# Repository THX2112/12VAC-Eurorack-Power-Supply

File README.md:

# 12VAC-Eurorack-Power-Supply
A simple +12 -12 power supply for Eurorack using 12VAC adapters

Based on:
http://www.musicfromouterspace.com/analogsynth_new/WALLWARTSUPPLY/WALLWARTSUPPLY.php

http://www.diystompboxes.com/smfforum/index.php?topic=28842.0

http://www.geofex.com/Article_Folders/Power-supplies/powersup.htm

BOM:

6   1n4007     DIODE

1              M05X2SHD        2X5-SHROUDED Header 5x2    

4   1000uF 50V POLARIZED CAPACITOR

2   100uF 35V  POLARIZED CAPACITOR

2   1uF        POLARIZED CAPACITOR

1   2k         RESISTOR

1   7812       TO220       Positive VOLTAGE REGULATOR          

1   7912       TO220       Negative VOLTAGE REGULATOR

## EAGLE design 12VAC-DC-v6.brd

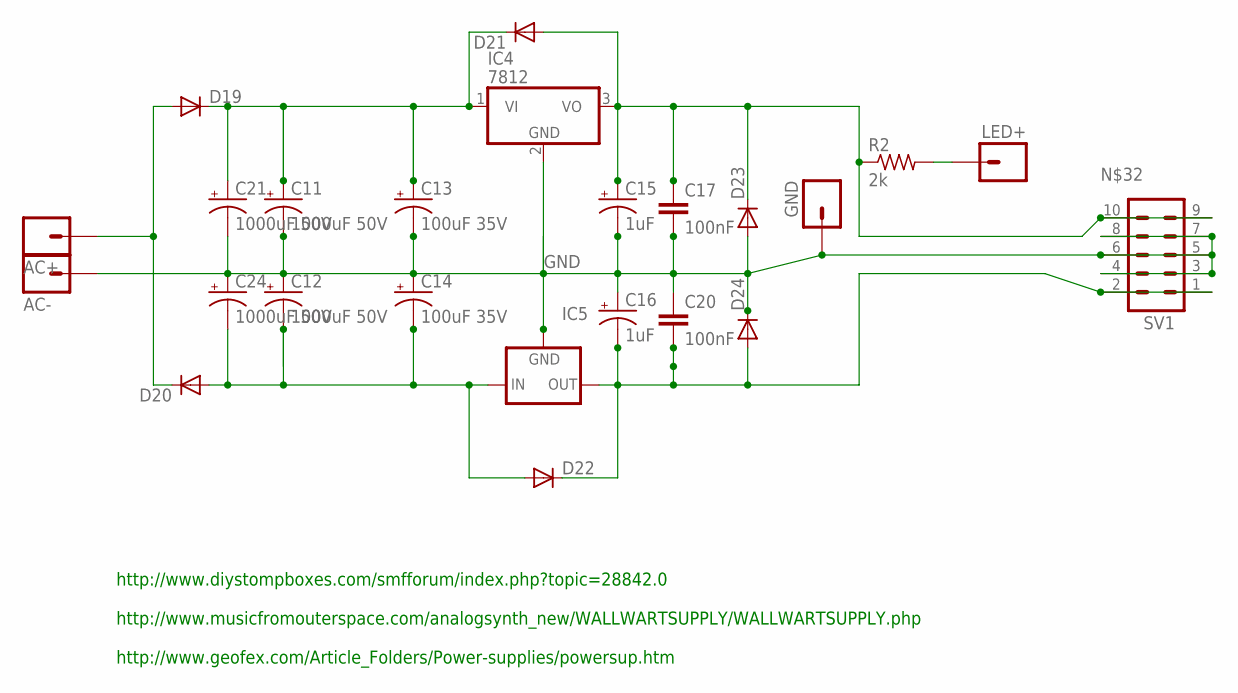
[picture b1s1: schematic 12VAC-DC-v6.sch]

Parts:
C11, C12, C21, C24: 1000uF 50V; E5-13
C13, C14: 100uF 35V; E2,5-6
C15, C16: 1uF; E2,5-5
C17, C20: 100nF; C025-024X044
D19, D20: DIODE-D-7.5; D-7.5
D21, D22, D24: DIODE-D-5; D-5
D23: DIODE-D-2.5; D-2.5
IC4: 7812; TO220V
IC5: 79XXS
JP6: AC+; 1X01_LONGPAD
JP22: AC-; 1X01_LONGPAD
JP25: GND; 1X01_LONGPAD
JP26: LED+; 1X01_LONGPAD
R2: 2k; 0204V
SV1: M05X2SHD; 2X5-SHROUDED

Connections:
GND: C11.-, C12.+, C13.-, C14.+, C15.-, C16.+, C17.2, C20.1, C21.-, C24.+, D23.A, D24.C, IC4.2 (GND), IC5.GND, JP22.1, JP25.1, SV1.3, SV1.4, SV1.5, SV1.6, SV1.7, SV1.8
unnamed: C11.+, C13.+, C21.+, D19.C, D21.C, IC4.1 (VI)
unnamed: C15.+, C17.1, D21.A, D23.C, IC4.3 (VO), R2.1, SV1.9, SV1.10
unnamed: C16.-, C20.2, D22.C, D24.A, IC5.OUT, SV1.1, SV1.2
unnamed: C12.-, C14.-, C24.-, D20.A, D22.A, IC5.IN
unnamed: D19.A, D20.C, JP6.1
unnamed: JP26.1, R2.2

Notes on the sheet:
http://www.diystompboxes.com/smfforum/index.php?topic=28842.0 http://www.musicfromouterspace.com/analogsynth_new/WALLWARTSUPPLY/WALLWARTSUPPLY.php http://www.geofex.com/Article_Folders/Power-supplies/powersup.htm

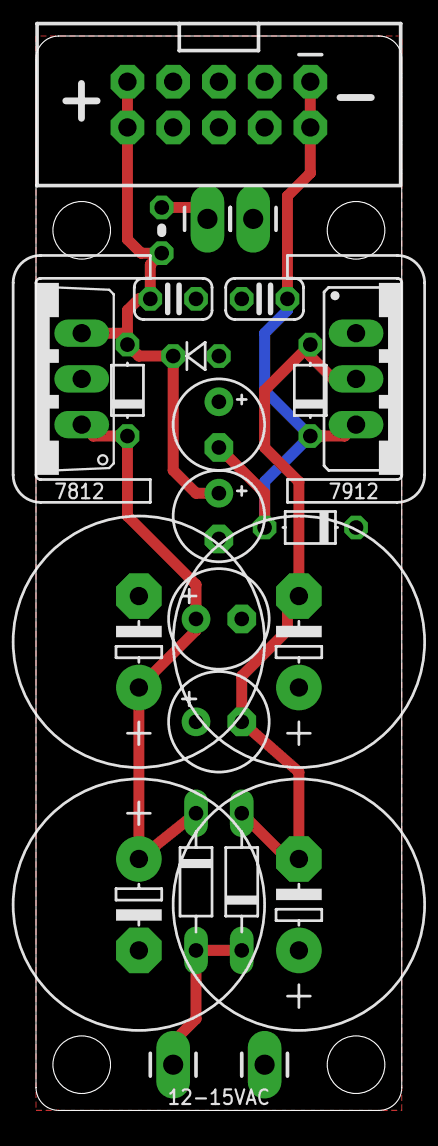
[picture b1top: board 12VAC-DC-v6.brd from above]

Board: 2 copper layers, 20.3 x 59.7 mm, 27 parts (0 on the bottom side), 7 nets.

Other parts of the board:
U$13: SYINSI-LOGO-2-MED-SILK-REV
U$14, U$15: D03S
